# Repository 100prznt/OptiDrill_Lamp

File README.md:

# Drill Press Light
 
LED lamp for mounting on a table or stand drill with a 60 mm rail.

The repository contains Eagle CAD data and a complete set of [Gerber data](https://github.com/100prznt/OptiDrill_Lamp/blob/main/LedPanel/LedPanel_v010__GERBER.zip?raw=true).

You can find the STL files for the case on PrusaPrinters.org
* [Drill Press Ligth on PrusaPrinters.org](https://www.prusaprinters.org/de/prints/125545-drill-press-light)

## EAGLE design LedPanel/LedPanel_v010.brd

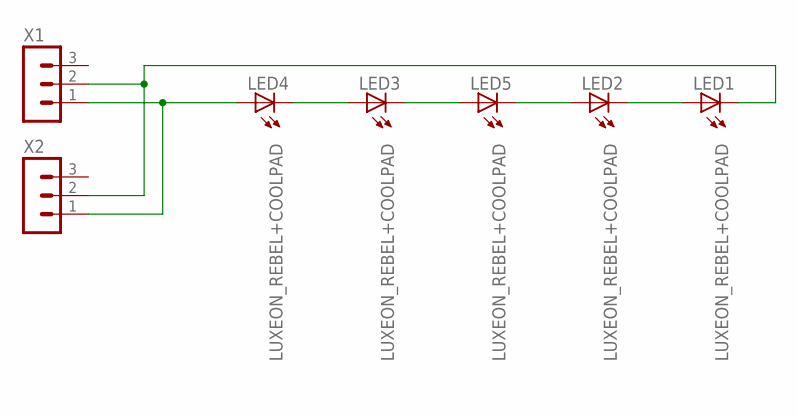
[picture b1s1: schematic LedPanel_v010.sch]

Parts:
LED1, LED2, LED3, LED4, LED5: LUXEON_REBEL+COOLPAD
X1, X2: MA03-1

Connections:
LED_A: LED4.A, LED4.A@1 (A), X1.1, X2.1
LED_K: LED1.C, LED1.C@1 (C), X1.2, X2.2
unnamed: LED1.A, LED1.A@1 (A), LED2.C, LED2.C@1 (C)
unnamed: LED2.A, LED2.A@1 (A), LED5.C, LED5.C@1 (C)
unnamed: LED3.C, LED3.C@1 (C), LED5.A, LED5.A@1 (A)
unnamed: LED3.A, LED3.A@1 (A), LED4.C, LED4.C@1 (C)
TH: LED1.TH, LED1.TH@1 (TH), LED1.TH@2 (TH), LED1.TH@3 (TH), LED1.TH@4 (TH), LED1.TH@5 (TH), LED1.TH@6 (TH), LED1.TH@7 (TH), LED1.TH@8 (TH), LED1.TH@9 (TH), LED1.TH@10 (TH), LED1.TH@11 (TH), LED1.TH@12 (TH), LED1.TH@13 (TH), LED1.TH@14 (TH), LED1.TH@15 (TH), LED1.TH@16 (TH), LED1.TH@17 (TH), LED1.TH@18 (TH), LED1.TH@19 (TH), LED1.TH@20 (TH), LED1.TH@21 (TH), LED1.TH@22 (TH), LED1.TH@23 (TH), LED1.TH@24 (TH), LED1.TH@25 (TH), LED1.TH@26 (TH), LED1.TH@27 (TH), LED1.TH@28 (TH), LED1.TH@29 (TH), LED1.TH@30 (TH), LED1.TH@31 (TH), LED1.TH@32 (TH), LED1.TH@33 (TH), LED1.TH@34 (TH), LED1.TH@35 (TH), LED2.TH, LED2.TH@1 (TH), LED2.TH@2 (TH), LED2.TH@3 (TH), LED2.TH@4 (TH), LED2.TH@5 (TH), LED2.TH@6 (TH), LED2.TH@7 (TH), LED2.TH@8 (TH), LED2.TH@9 (TH), LED2.TH@10 (TH), LED2.TH@11 (TH), LED2.TH@12 (TH), LED2.TH@13 (TH), LED2.TH@14 (TH), LED2.TH@15 (TH), LED2.TH@16 (TH), LED2.TH@17 (TH), LED2.TH@18 (TH), LED2.TH@19 (TH), LED2.TH@20 (TH), LED2.TH@21 (TH), LED2.TH@22 (TH), LED2.TH@23 (TH), LED2.TH@24 (TH), LED2.TH@25 (TH), LED2.TH@26 (TH), LED2.TH@27 (TH), LED2.TH@28 (TH), LED2.TH@29 (TH), LED2.TH@30 (TH), LED2.TH@31 (TH), LED2.TH@32 (TH), LED2.TH@33 (TH), LED2.TH@34 (TH), LED2.TH@35 (TH), LED3.TH, LED3.TH@1 (TH), LED3.TH@2 (TH), LED3.TH@3 (TH), LED3.TH@4 (TH), LED3.TH@5 (TH), LED3.TH@6 (TH), LED3.TH@7 (TH), LED3.TH@8 (TH), LED3.TH@9 (TH), LED3.TH@10 (TH), LED3.TH@11 (TH), LED3.TH@12 (TH), LED3.TH@13 (TH), LED3.TH@14 (TH), LED3.TH@15 (TH), LED3.TH@16 (TH), LED3.TH@17 (TH), LED3.TH@18 (TH), LED3.TH@19 (TH), LED3.TH@20 (TH), LED3.TH@21 (TH), LED3.TH@22 (TH), LED3.TH@23 (TH), LED3.TH@24 (TH), LED3.TH@25 (TH), LED3.TH@26 (TH), LED3.TH@27 (TH), LED3.TH@28 (TH), LED3.TH@29 (TH), LED3.TH@30 (TH), LED3.TH@31 (TH), LED3.TH@32 (TH), LED3.TH@33 (TH), LED3.TH@34 (TH), LED3.TH@35 (TH), LED4.TH, LED4.TH@1 (TH), LED4.TH@2 (TH), LED4.TH@3 (TH), LED4.TH@4 (TH), LED4.TH@5 (TH), LED4.TH@6 (TH), LED4.TH@7 (TH), LED4.TH@8 (TH), LED4.TH@9 (TH), LED4.TH@10 (TH), LED4.TH@11 (TH), LED4.TH@12 (TH), LED4.TH@13 (TH), LED4.TH@14 (TH), LED4.TH@15 (TH), LED4.TH@16 (TH), LED4.TH@17 (TH), LED4.TH@18 (TH), LED4.TH@19 (TH), LED4.TH@20 (TH), LED4.TH@21 (TH), LED4.TH@22 (TH), LED4.TH@23 (TH), LED4.TH@24 (TH), LED4.TH@25 (TH), LED4.TH@26 (TH), LED4.TH@27 (TH), LED4.TH@28 (TH), LED4.TH@29 (TH), LED4.TH@30 (TH), LED4.TH@31 (TH), LED4.TH@32 (TH), LED4.TH@33 (TH), LED4.TH@34 (TH), LED4.TH@35 (TH), LED5.TH, LED5.TH@1 (TH), LED5.TH@2 (TH), LED5.TH@3 (TH), LED5.TH@4 (TH), LED5.TH@5 (TH), LED5.TH@6 (TH), LED5.TH@7 (TH), LED5.TH@8 (TH), LED5.TH@9 (TH), LED5.TH@10 (TH), LED5.TH@11 (TH), LED5.TH@12 (TH), LED5.TH@13 (TH), LED5.TH@14 (TH), LED5.TH@15 (TH), LED5.TH@16 (TH), LED5.TH@17 (TH), LED5.TH@18 (TH), LED5.TH@19 (TH), LED5.TH@20 (TH), LED5.TH@21 (TH), LED5.TH@22 (TH), LED5.TH@23 (TH), LED5.TH@24 (TH), LED5.TH@25 (TH), LED5.TH@26 (TH), LED5.TH@27 (TH), LED5.TH@28 (TH), LED5.TH@29 (TH), LED5.TH@30 (TH), LED5.TH@31 (TH), LED5.TH@32 (TH), LED5.TH@33 (TH), LED5.TH@34 (TH), LED5.TH@35 (TH)

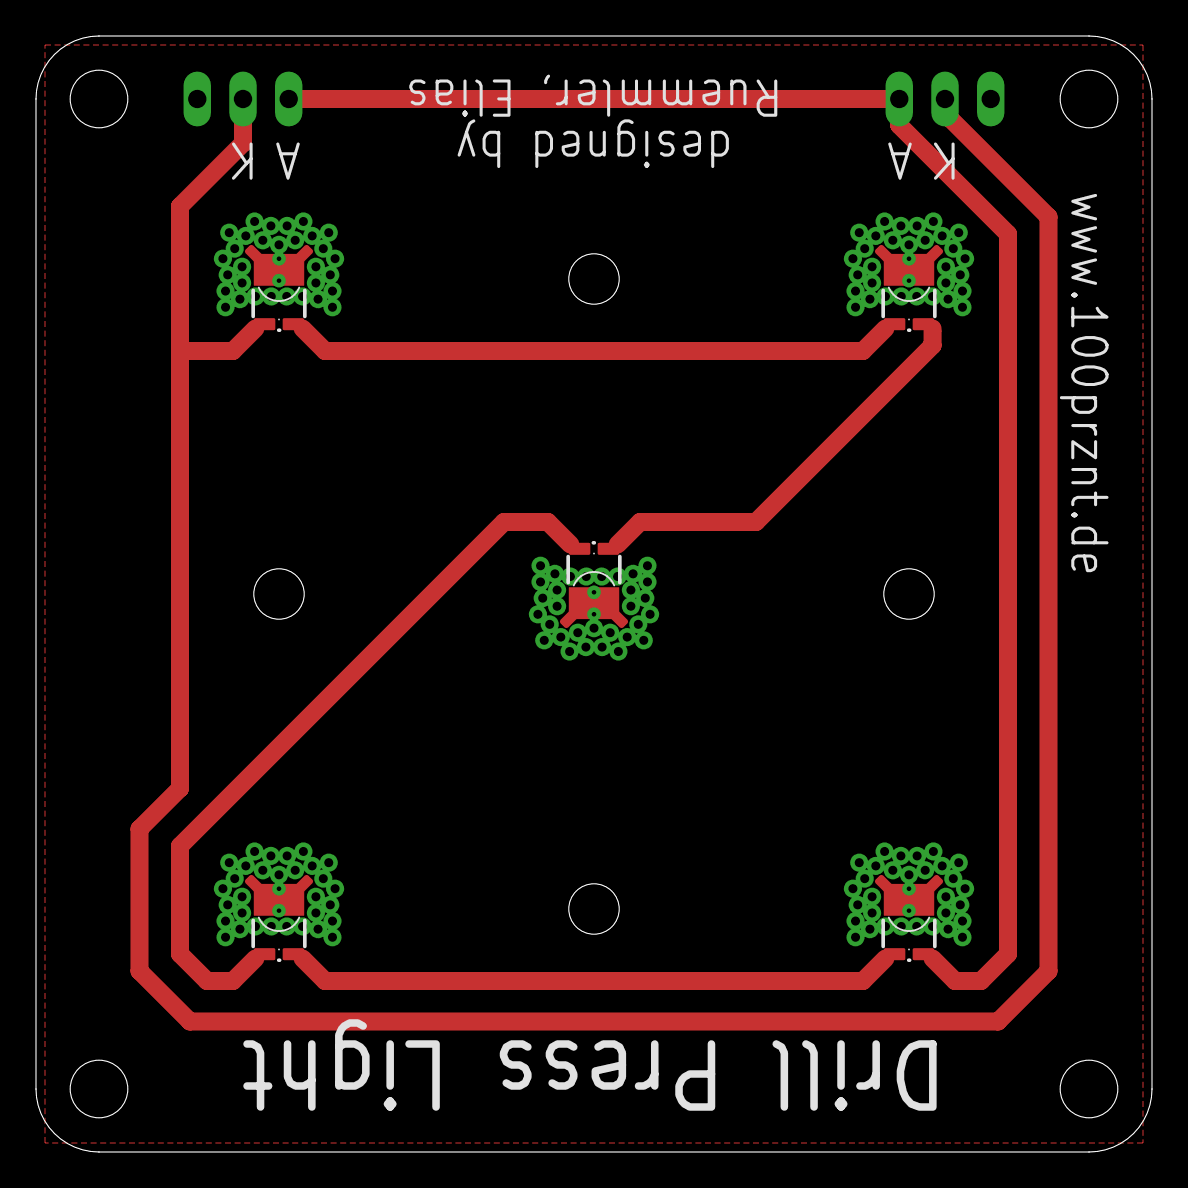
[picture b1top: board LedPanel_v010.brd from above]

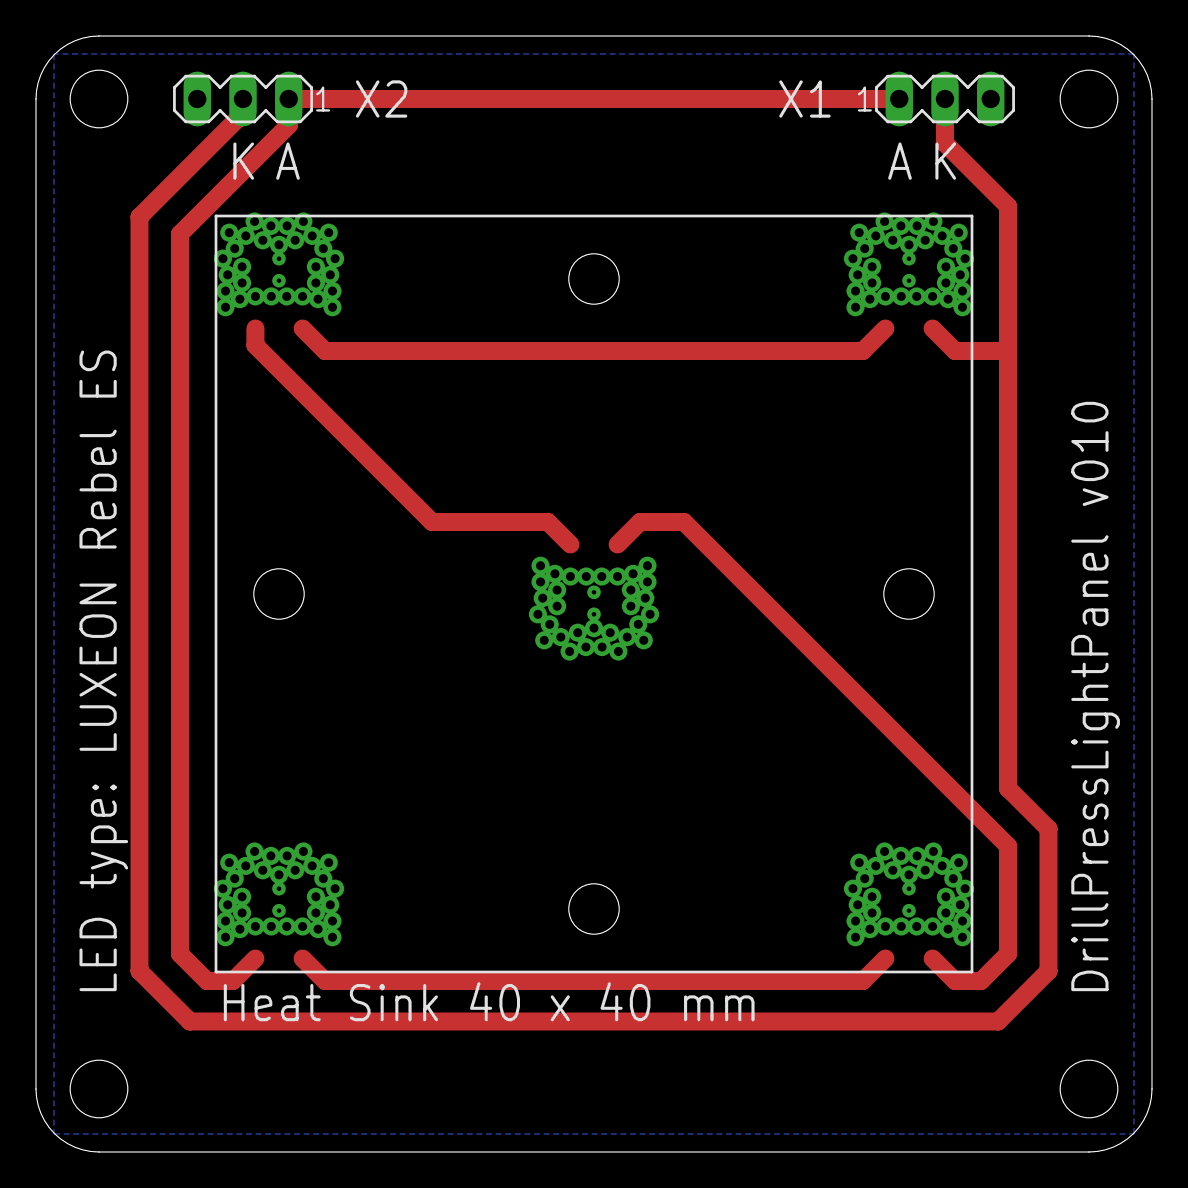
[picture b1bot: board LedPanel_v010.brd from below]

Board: 2 copper layers, 62.0 x 62.0 mm, 7 parts (2 on the bottom side), 7 nets.

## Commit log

2022-01-28 restruct
